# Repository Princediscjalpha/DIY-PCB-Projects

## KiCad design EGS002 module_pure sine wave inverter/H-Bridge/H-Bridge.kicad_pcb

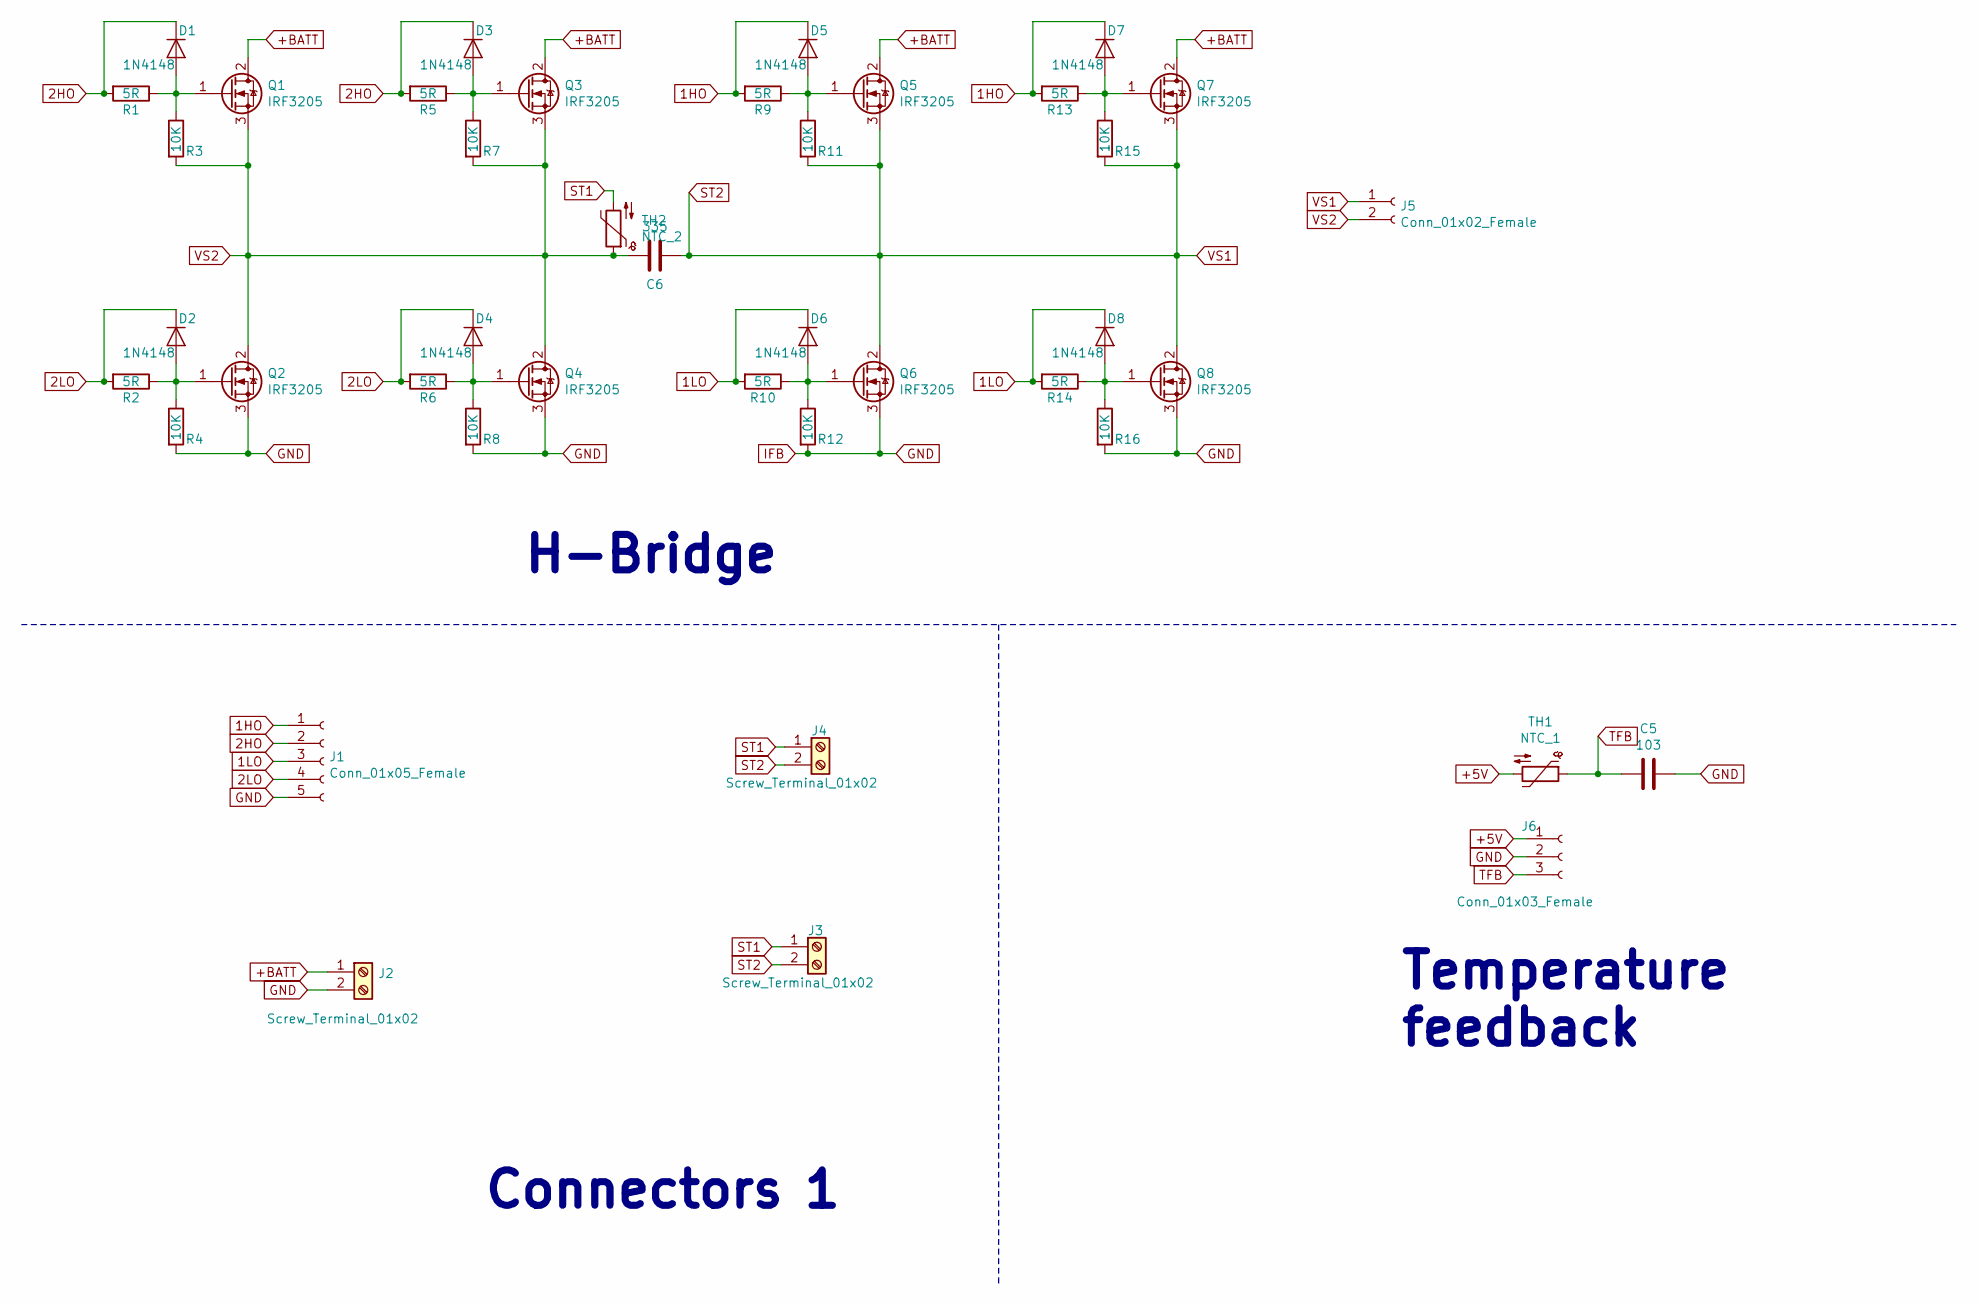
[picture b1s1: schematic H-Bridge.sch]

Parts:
C5: 103; C_Disc_D7.5mm_W5.0mm_P5.00mm
C6: 335; C_Rect_L13.0mm_W3.0mm_P10.00mm_FKS3_FKP3_MKS4
D1, D2, D3, D4, D5, D6, D7, D8: 1N4148; D_DO-35_SOD27_P2.54mm_Vertical_KathodeUp
J1: Conn_01x05_Female; PinSocket_1x05_P2.54mm_Vertical
J2, J3, J4: Screw_Terminal_01x02; TerminalBlock_Altech_AK300-2_P5.00mm
J5: Conn_01x02_Female; PinSocket_1x02_P2.54mm_Vertical
J6: Conn_01x03_Female; PinSocket_1x03_P2.54mm_Vertical
Q1, Q2, Q3, Q4, Q5, Q6, Q7, Q8: IRF3205; TO-220-3_Vertical
R1, R2, R5, R6, R9, R10, R13, R14: 5R; R_Axial_DIN0207_L6.3mm_D2.5mm_P10.16mm_Horizontal
R3, R4, R7, R8, R11, R12, R15, R16: 10K; R_Axial_DIN0207_L6.3mm_D2.5mm_P10.16mm_Horizontal
TH1: NTC_1; C_Disc_D7.5mm_W5.0mm_P5.00mm
TH2: NTC_2; C_Disc_D7.5mm_W5.0mm_P5.00mm

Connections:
1HO: D5.1 (K), D7.1 (K), J1.1, R9.2, R13.2
1LO: D6.1 (K), D8.1 (K), J1.3, R10.2, R14.2
2HO: D1.1 (K), D3.1 (K), J1.2, R1.2, R5.2
2LO: D2.1 (K), D4.1 (K), J1.4, R2.2, R6.2
+5V: J6.1, TH1.2
+BATT: J2.1, Q1.2 (D), Q3.2 (D), Q5.2 (D), Q7.2 (D)
GND: C5.1, J1.5, J2.2, J6.2, Q2.3 (S), Q4.3 (S), Q6.3 (S), Q8.3 (S), R4.2, R8.2, R12.2, R16.2
unnamed: D1.2 (A), Q1.1 (G), R1.1, R3.1
unnamed: D2.2 (A), Q2.1 (G), R2.1, R4.1
unnamed: D3.2 (A), Q3.1 (G), R5.1, R7.1
unnamed: D4.2 (A), Q4.1 (G), R6.1, R8.1
unnamed: D5.2 (A), Q5.1 (G), R9.1, R11.1
unnamed: D6.2 (A), Q6.1 (G), R10.1, R12.1
unnamed: D7.2 (A), Q7.1 (G), R13.1, R15.1
unnamed: D8.2 (A), Q8.1 (G), R14.1, R16.1
ST1: J3.1, J4.1, TH2.2
ST2: C6.1, J3.2, J4.2, J5.1, Q5.3 (S), Q6.2 (D), Q7.3 (S), Q8.2 (D), R11.2, R15.2
TFB: C5.2, J6.3, TH1.1
VS2: C6.2, J5.2, Q1.3 (S), Q2.2 (D), Q3.3 (S), Q4.2 (D), R3.2, R7.2, TH2.1

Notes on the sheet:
H-Bridge
Connectors
Temperature feedback

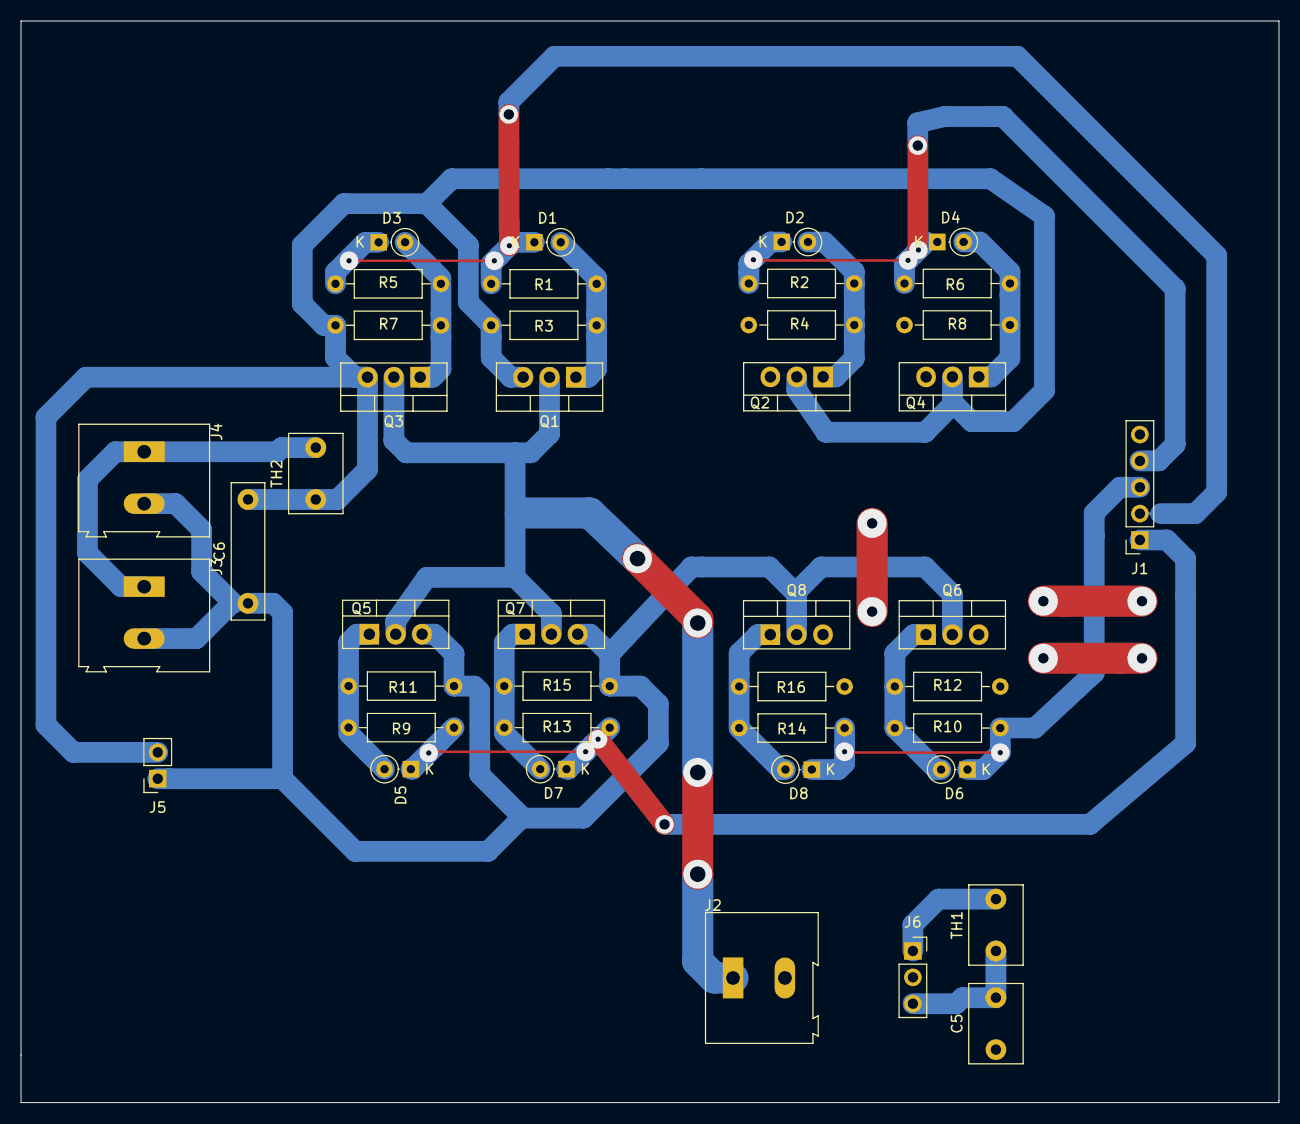
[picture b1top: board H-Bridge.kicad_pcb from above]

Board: 2 copper layers, 121.2 x 104.2 mm, 42 parts (0 on the bottom side), 19 nets.

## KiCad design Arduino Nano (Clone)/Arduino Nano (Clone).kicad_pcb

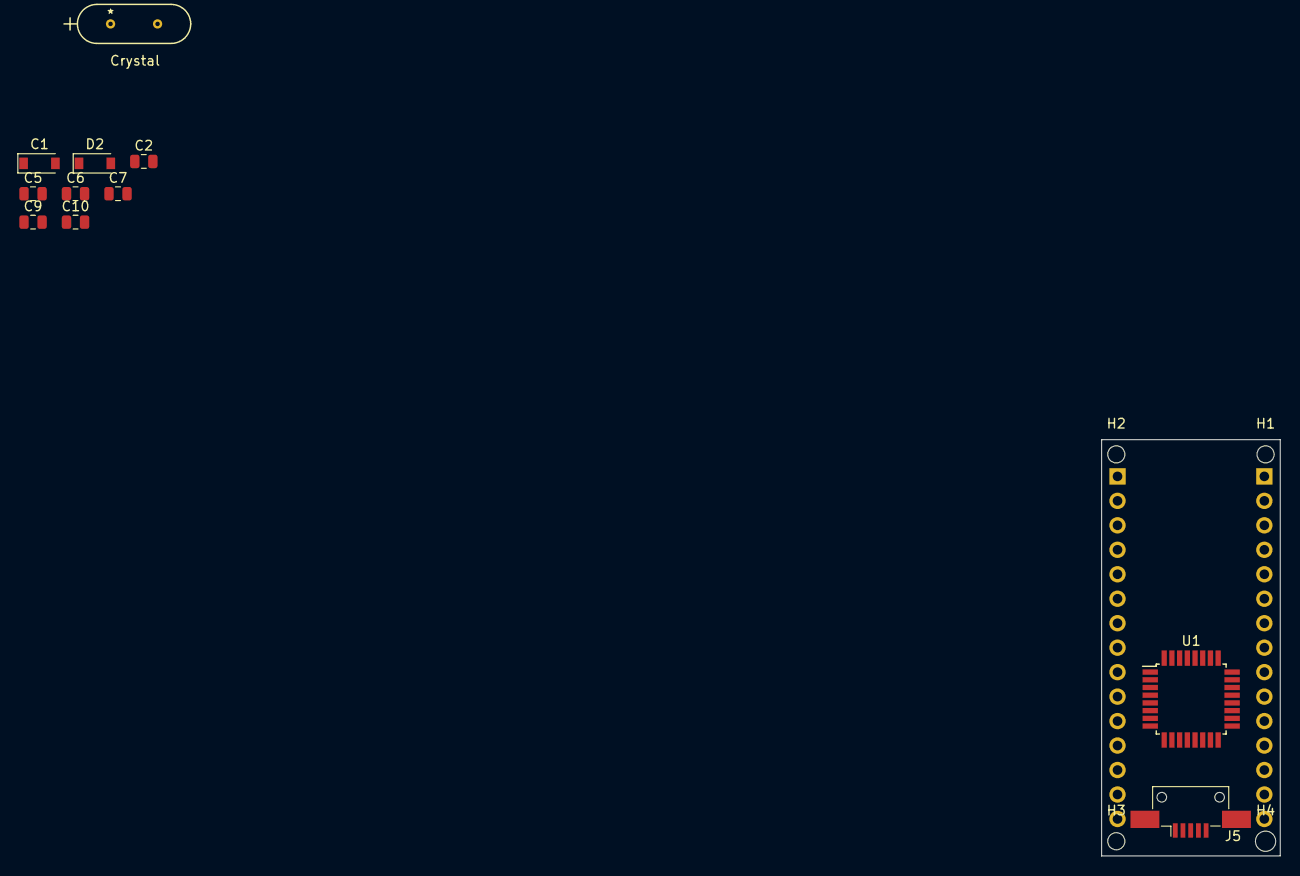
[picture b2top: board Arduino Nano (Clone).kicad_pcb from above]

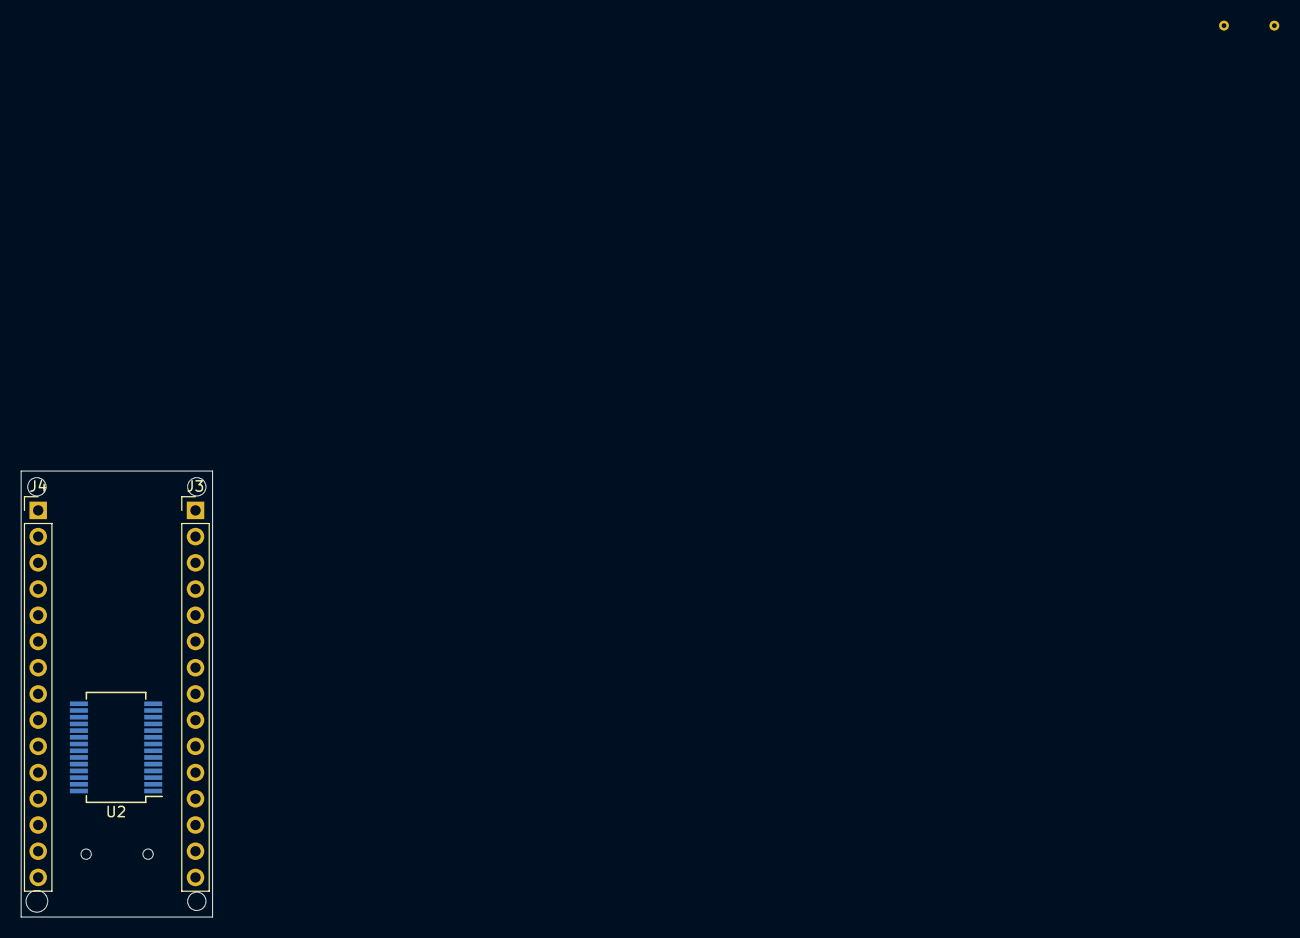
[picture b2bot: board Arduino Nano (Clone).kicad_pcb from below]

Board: 2 copper layers, 18.5 x 43.2 mm, 18 parts (3 on the bottom side), 33 nets, no tracks yet.

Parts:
C1: C; D_SOD-123
C2, C5, C6, C7, C9, C10: C; C_0805_2012Metric
D2: MBR0520; D_SOD-123
H1, H2, H3, H4: MountingHole; MountingHole_2.1mm
J3, J4: Conn_01x15_Male; PinHeader_1x15_P2.54mm_Vertical
J5: USB_B_Mini; USB_Mini-B_AdamTech_MUSB-B5-S-VT-TSMT-1_SMD_Vertical
U1: ATmega168-20AU; TQFP-32_7x7mm_P0.8mm
U2: FT232RL; SSOP-28_5.3x10.2mm_P0.65mm
Y1: Crystal; ABL-16.000MHZ-B2

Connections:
+3V3: C7.1, J4.14, U2.17
+5V: C5.1, D2.1, J4.4, U1.4, U1.6, U1.18, U2.4, U2.20
A0: J4.5, U1.23
A1: J4.6, U1.24
A2: J4.7, U1.25
A3: J4.8, U1.26
A4: J4.9, U1.27
A5: J4.10, U1.28
A6: J4.11, U1.19
A7: J4.12, U1.22
A_REF: C10.1, J4.13, U1.20
D0_RX: J3.2, U1.30
D1_TX: J3.1, U1.31
D2: J3.5, U1.32
D3: J3.6, U1.1
D4: J3.7, U1.2
D5: J3.8, U1.9
D6: J3.9, U1.10
D7: J3.10, U1.11
D8: J3.11, U1.12
D9: J3.12, U1.13
D10: J3.13, U1.14
D11_MOSI: J3.14, U1.15
D12_MISO: J3.15, U1.16
D13_SCK: J4.15, U1.17
GND: C1.2, C2.2, C5.2, C7.2, C9.2, C10.2, J3.4, J4.2, U1.3, U1.5, U1.21, U2.7, U2.18, U2.21, U2.25
unnamed: C6.1, U2.2
RST: J3.3, J4.3, U1.29
USB_DM: J5.2, U2.16
USB_DP: J5.3, U2.15
V_USB: C9.1, D2.2
XTAL_1: C1.1, U1.7, Y1.1
XTAL_2: C2.1, U1.8, Y1.2

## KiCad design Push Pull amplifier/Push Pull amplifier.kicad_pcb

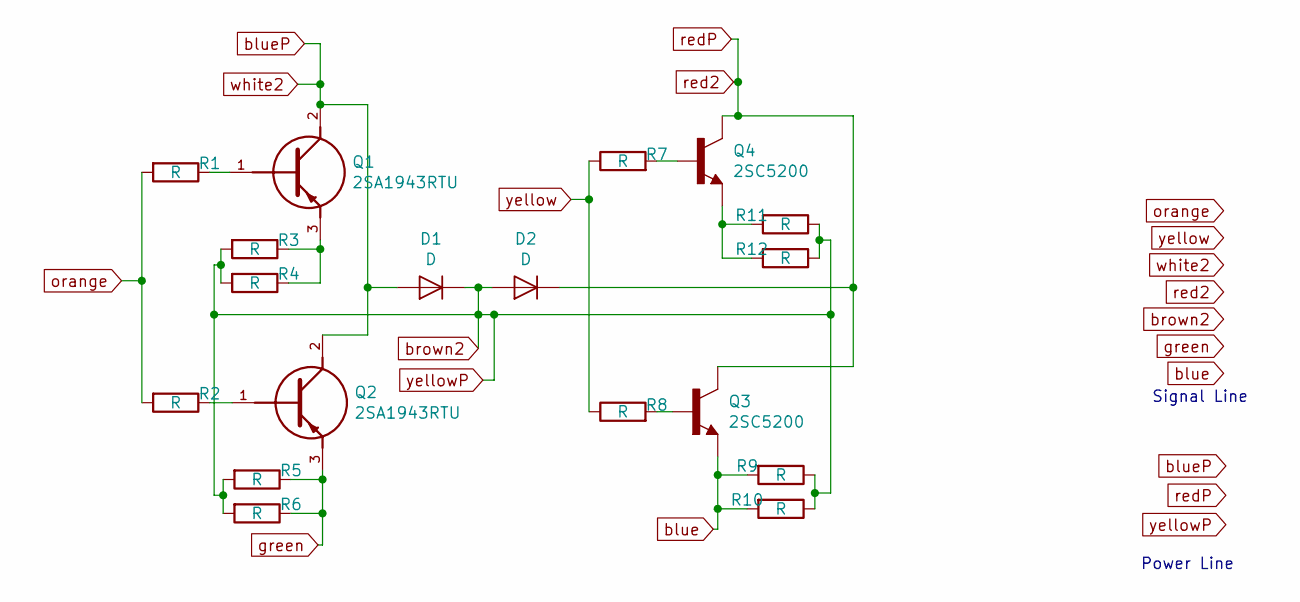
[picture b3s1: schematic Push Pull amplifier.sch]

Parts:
D1, D2: D; D_5KPW_P7.62mm_Vertical_AnodeUp
Q1, Q2: 2SA1943RTU; TO545P520X2000X2900-3P
Q3, Q4: 2SC5200; TO545P2020X520X2910-3
R1, R2, R3, R4, R5, R6, R7, R8, R9, R10, R11, R12: R; R_Axial_DIN0204_L3.6mm_D1.6mm_P5.08mm_Horizontal

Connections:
unnamed: Q1.1 (B), R1.1
unnamed: Q1.3 (E), R3.1, R4.1
unnamed: Q2.1 (B), R2.1
unnamed: Q3.1 (B), R8.2
unnamed: Q4.1 (B), R7.2
unnamed: Q4.3 (E), R11.2, R12.2
blue: Q3.3 (E), R9.2, R10.2
blueP: D1.2 (A), Q1.2 (C), Q2.2 (C)
brown2: D1.1 (K), D2.2 (A), R3.2, R4.2, R5.2, R6.2, R9.1, R10.1, R11.1, R12.1
green: Q2.3 (E), R5.1, R6.1
orange: R1.2, R2.2
red2: D2.1 (K), Q3.2 (C), Q4.2 (C)
yellow: R7.1, R8.1

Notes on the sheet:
Power Line
Signal Line

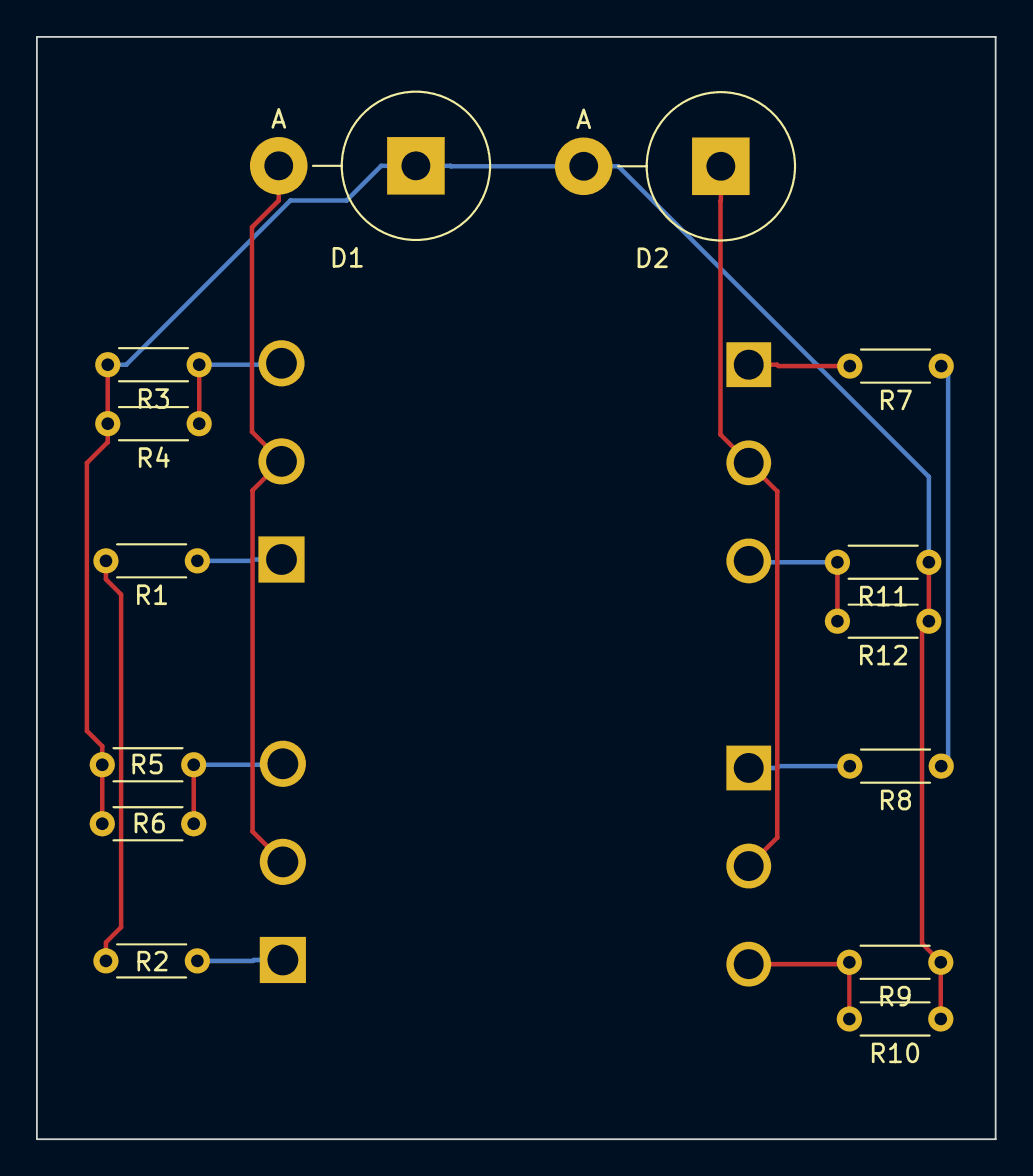
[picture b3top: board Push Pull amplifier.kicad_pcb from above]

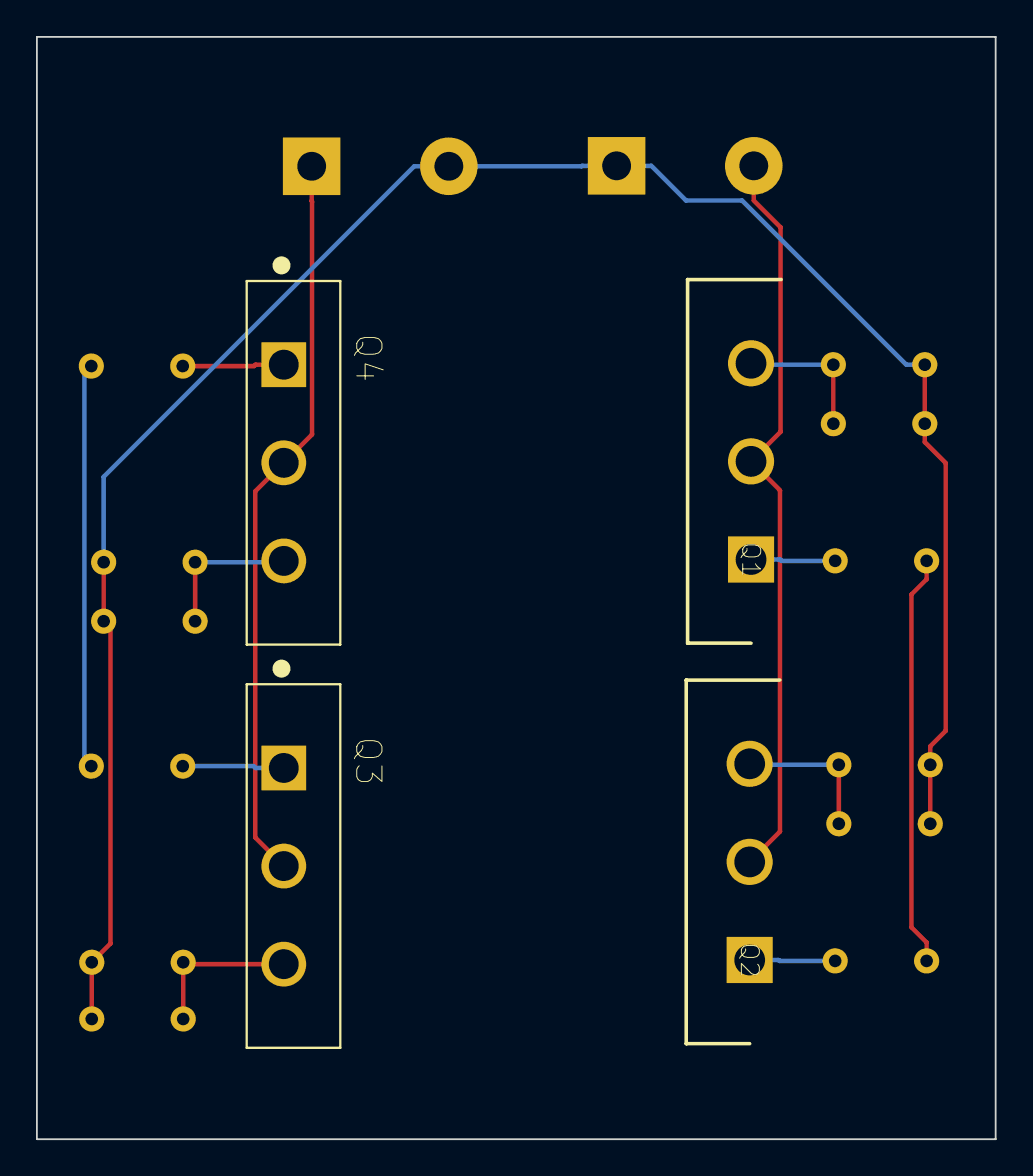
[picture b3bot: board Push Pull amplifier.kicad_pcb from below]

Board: 2 copper layers, 53.3 x 61.2 mm, 18 parts (4 on the bottom side), 13 nets.

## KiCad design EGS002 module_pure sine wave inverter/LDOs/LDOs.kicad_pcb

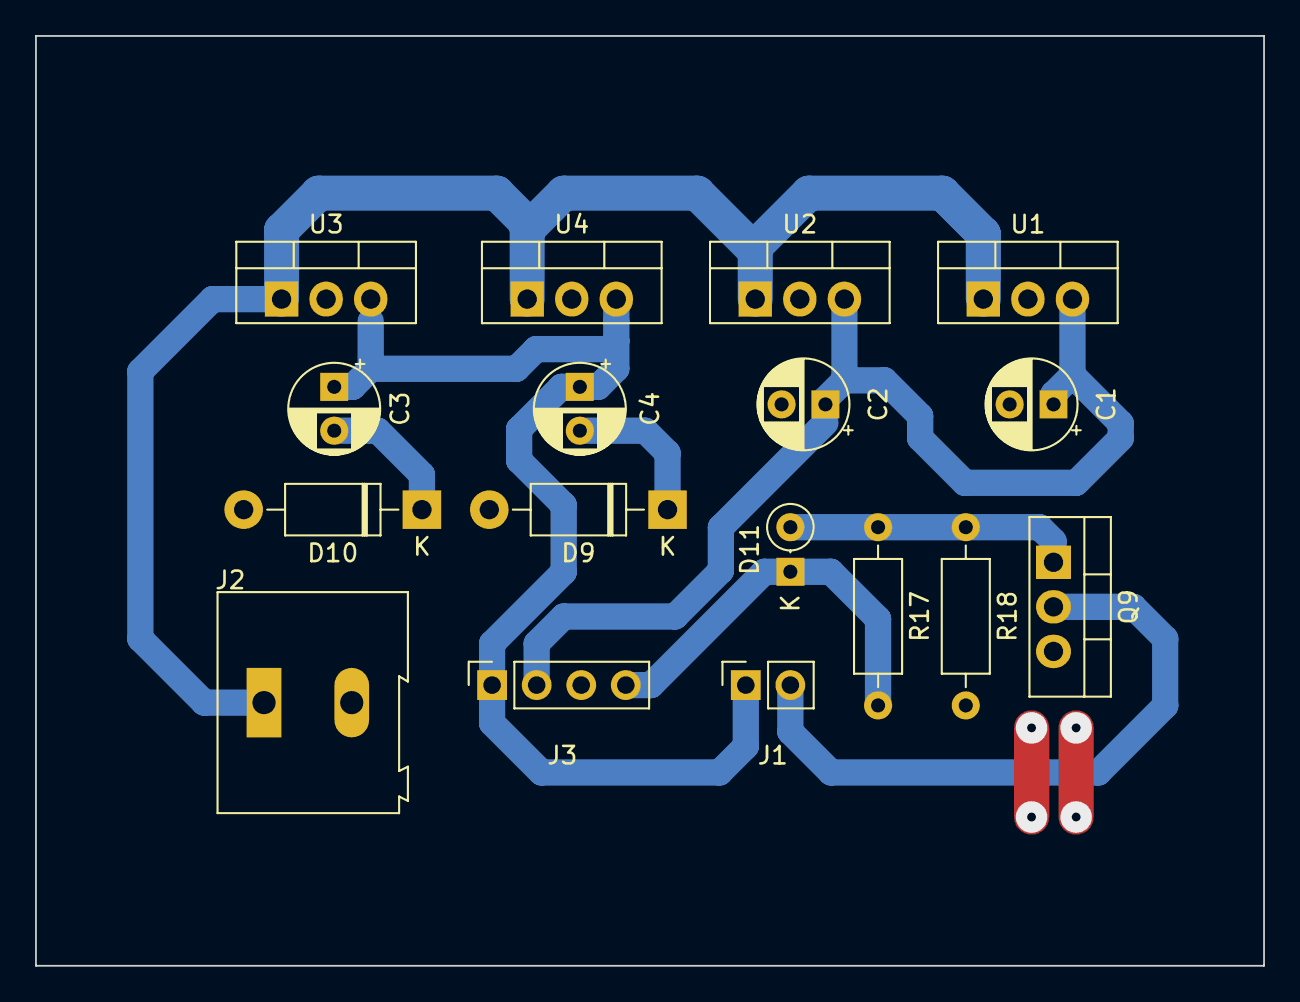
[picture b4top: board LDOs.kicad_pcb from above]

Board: 2 copper layers, 70.0 x 53.0 mm, 17 parts (0 on the bottom side), 9 nets.

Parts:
C1, C2, C3, C4: CP; CP_Radial_D5.0mm_P2.50mm
D9, D10: 1N4007; D_DO-41_SOD81_P10.16mm_Horizontal
D11: 1N4148; D_DO-35_SOD27_P2.54mm_Vertical_KathodeUp
J1: Conn_01x02_Female; PinSocket_1x02_P2.54mm_Vertical
J2: Screw_Terminal_01x02; TerminalBlock_Altech_AK300-2_P5.00mm
J3: Conn_01x04_Female; PinSocket_1x04_P2.54mm_Vertical
Q9: IRF3205; TO-220-3_Vertical
R17: 2.2K; R_Axial_DIN0207_L6.3mm_D2.5mm_P10.16mm_Horizontal
R18: 10K; R_Axial_DIN0207_L6.3mm_D2.5mm_P10.16mm_Horizontal
U1, U2: L7805; TO-220-3_Vertical
U3, U4: L7812; TO-220-3_Vertical

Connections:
+5V: C1.1, C2.1, J3.2, U1.3, U2.3
+12V: C3.1, C4.1, J1.1, J3.1, U3.3, U4.3
+BATT: J2.1, U1.1, U2.1, U3.1, U4.1
F-: J1.2, Q9.2
FANCTR: D11.1, J3.4, R17.2
GND: C1.2, C2.2, D9.2, D10.2, J2.2, J3.3, Q9.3, R18.2, U1.2, U2.2, U3.2, U4.2
unnamed: C3.2, D10.1
unnamed: C4.2, D9.1
unnamed: D11.2, Q9.1, R17.1, R18.1

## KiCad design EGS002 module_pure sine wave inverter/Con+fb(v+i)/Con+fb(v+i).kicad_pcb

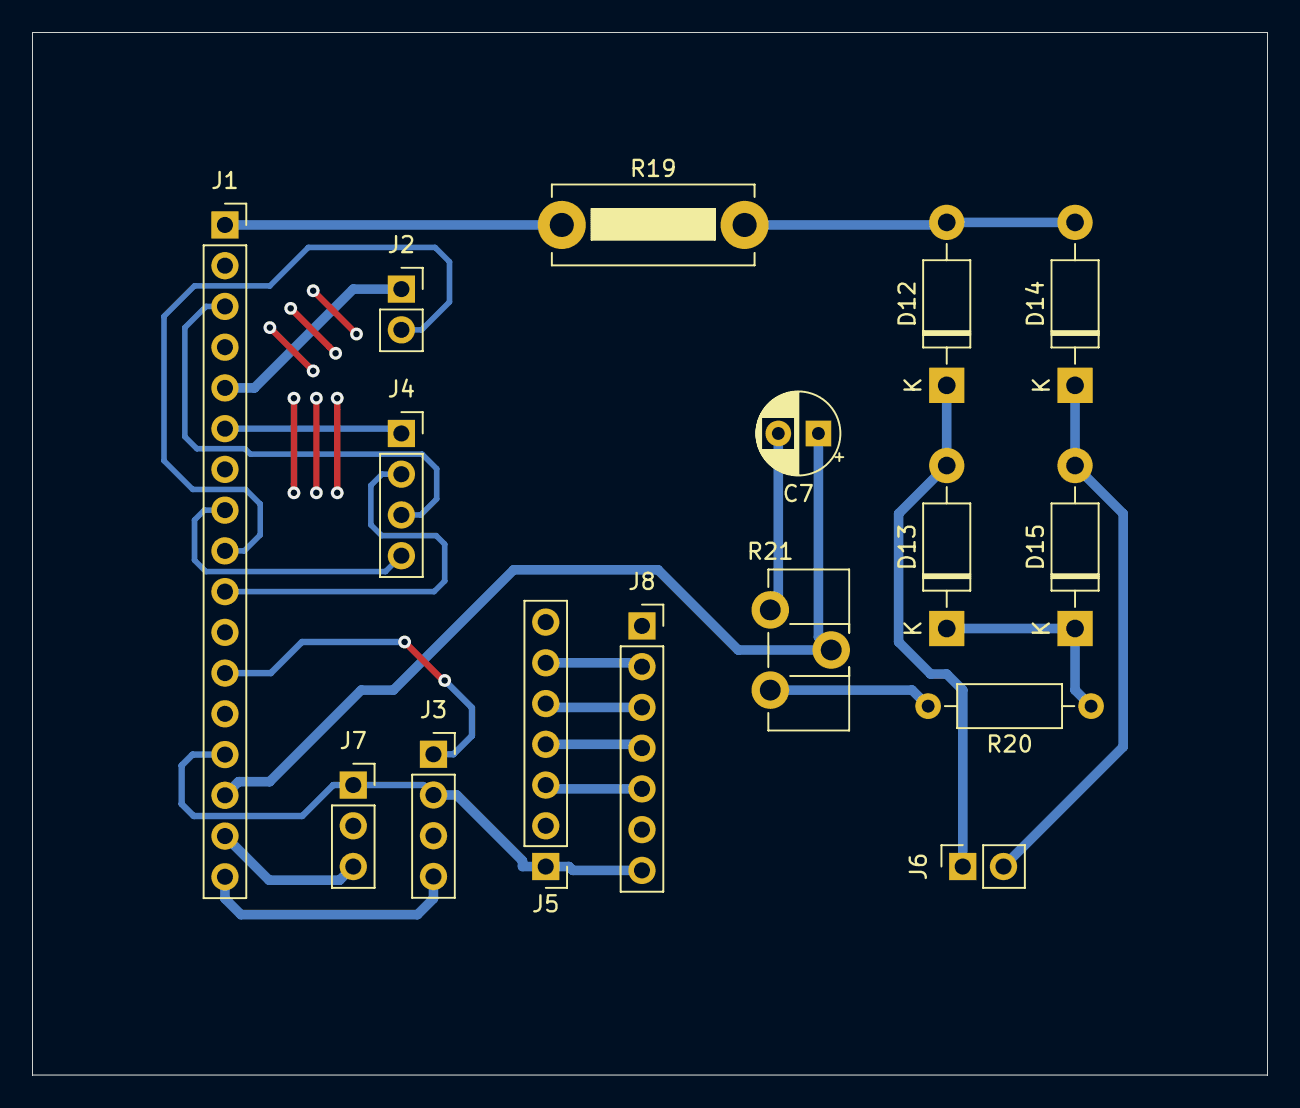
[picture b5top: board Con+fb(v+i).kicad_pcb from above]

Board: 2 copper layers, 77.0 x 65.0 mm, 16 parts (0 on the bottom side), 22 nets.

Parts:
C7: 4.7uF; CP_Radial_D5.0mm_P2.50mm
D12, D13, D14, D15: 1N4007; D_DO-41_SOD81_P10.16mm_Horizontal
J1: Conn_01x17_Female; PinSocket_1x17_P2.54mm_Vertical
J2, J6: Conn_01x02_Female; PinSocket_1x02_P2.54mm_Vertical
J3, J4: Conn_01x04_Female; PinSocket_1x04_P2.54mm_Vertical
J5: Conn_01x07_Male; PinHeader_1x07_P2.54mm_Vertical
J7: Conn_01x03_Female; PinSocket_1x03_P2.54mm_Vertical
J8: Conn_01x07_Female; PinSocket_1x07_P2.54mm_Vertical
R19: Shunt 0; R_Bare_Metal_Element_L12.4mm_W4.8mm_P11.40mm
R20: 4.7K; R_Axial_DIN0207_L6.3mm_D2.5mm_P10.16mm_Horizontal
R21: 10K; Potentiometer_ACP_CA9-H3,8_Horizontal

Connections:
1HO: J1.6, J4.1
1LO: J1.3, J4.3
2HO: J1.10, J4.2
2LO: J1.8, J4.4
+5V: J1.14, J3.2, J5.1, J7.1, J8.7
+12V: J1.12, J3.1
CS: J5.5, J8.3
FANCTR: J1.17, J3.4
GND: C7.2, J1.2, J1.4, J1.7, J1.11, J1.13, J3.3, J5.2, J5.7, J7.2, J8.1, J8.6, R21.1
IFB: J1.1, R19.1
LED+: J5.6, J8.2
unnamed: D12.2, D14.2, R19.2
unnamed: D13.1, D15.1, R20.1
unnamed: R20.2, R21.3
SCLK: J5.4, J8.4
SDI: J5.3, J8.5
ST1_J3: D12.1, D13.2, J6.1
ST2_J3: D14.1, D15.2, J6.2
TFB: J1.16, J7.3
VFB: C7.1, J1.15, R21.2
VS1: J1.5, J2.1
VS2: J1.9, J2.2

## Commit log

2020-06-07 added KiCAD PCB file for class AB amplifier based on SC5200 and SA1943 transistors (Note: this PCB only contains the amplifier board only you need to connect power supply and preamp to the circuit in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
2020-06-07 added arduino nano clone file with this you are able to make your own arduino nano clone model to learn how it works from scratch (Note: This project is under maintainence so I will try to update thi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
2020-06-07 added board file for coreless drone, with this project you are able to learn the basic prototyping of quadcopter it utilises gyrosensor, radio communication module connected alpong a microcontroller(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
2020-06-07 added board file for DIY Inveter/UPS using EGS002 module, with this project you are able to make your own AC Inverter/UPS from scratch and understand its working the PCB Layouts in this project are s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
2020-06-09 added datasheet for EGS8010 SPWM modulation and control IC
2020-06-21 added autorouter plugin for KiCad in support with latest version of JAVA

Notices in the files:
parts and their libraries:
Copyright 2016 Accelerated Designs. All rights reserved.
